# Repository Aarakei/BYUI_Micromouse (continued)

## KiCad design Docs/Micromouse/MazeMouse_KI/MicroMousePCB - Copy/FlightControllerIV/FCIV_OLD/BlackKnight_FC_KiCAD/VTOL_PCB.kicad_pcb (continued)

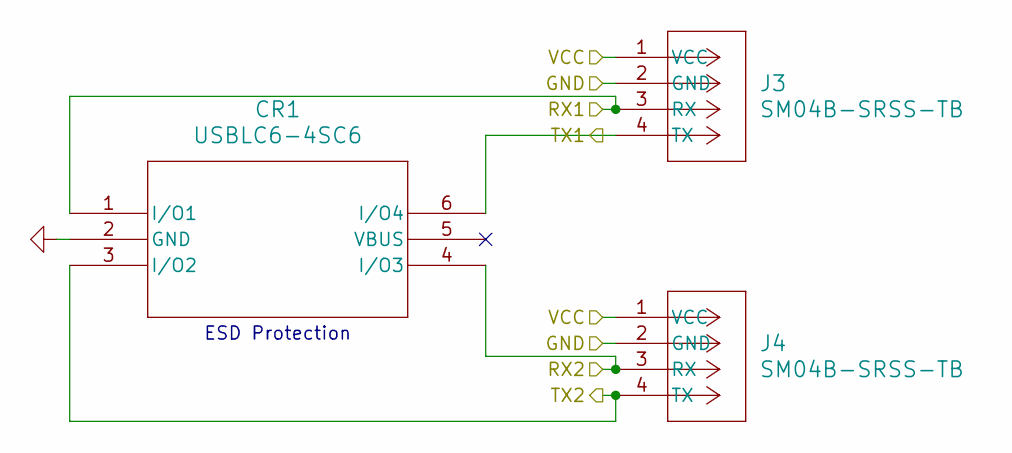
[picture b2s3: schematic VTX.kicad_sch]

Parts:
CR1: USBLC6-4SC6; SOT23-6L_STM; Manufacturer_Part_Number USBLC6-4SC6; JLCPCB Part # C111212
J3, J4: SM04B-SRSS-TB; JST_SH_SM04B-SRSS-TB_1x04-1MP_P1.00mm_Horizontal; Manufacturer_Part_Number XY-SM04B-SRSS-TB; JLCPCB Part # C160404

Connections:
9V_3A: J3.1 (VCC), J4.1 (VCC); also elsewhere on the board
/STM32F722VET6/UART4_RX: CR1.6 (I/O4), J3.4 (TX); also elsewhere on the board
/STM32F722VET6/UART4_TX: CR1.1 (I/O1), J3.3 (RX); also elsewhere on the board
/STM32F722VET6/USART2_RX: CR1.4 (I/O3), J4.3 (RX); also elsewhere on the board
/STM32F722VET6/USART2_TX: CR1.3 (I/O2), J4.4 (TX); also elsewhere on the board
GND: CR1.2 (GND), J3.2 (GND), J4.2 (GND); also elsewhere on the board

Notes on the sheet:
ESD Protection

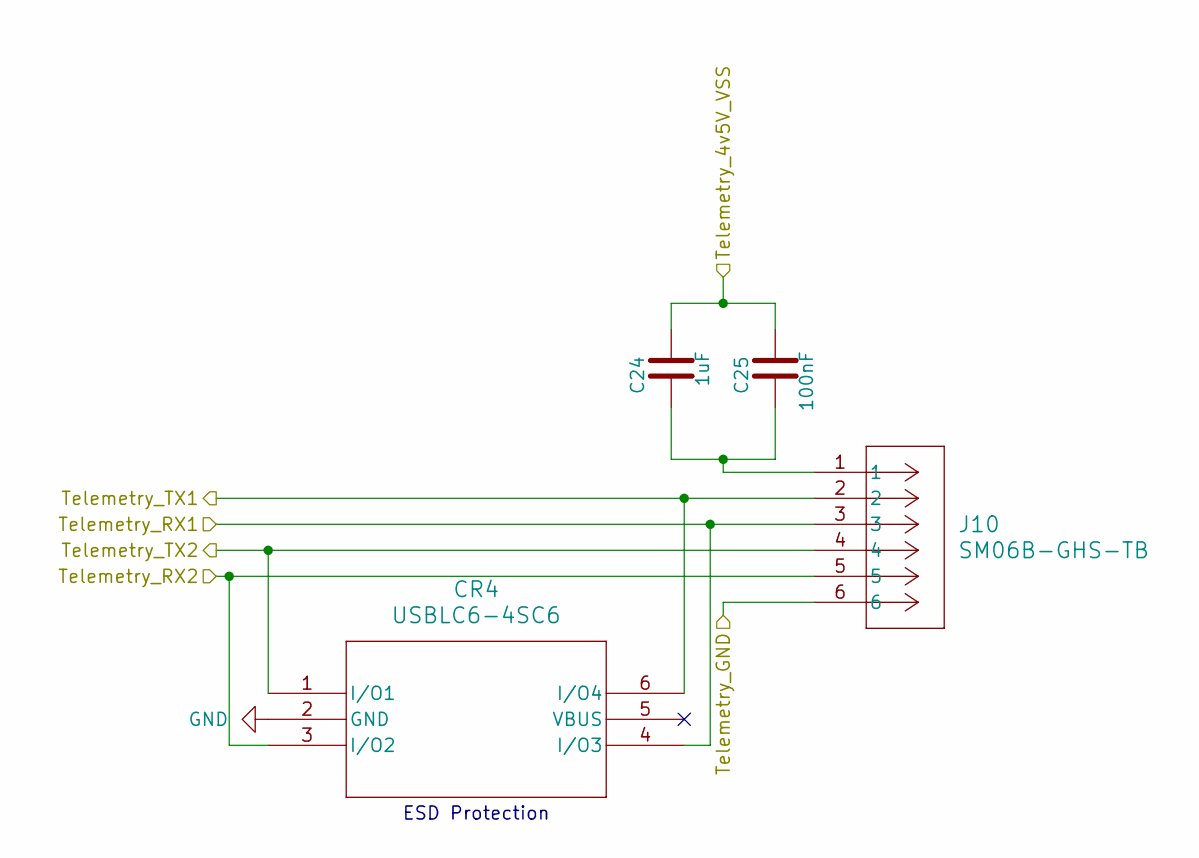
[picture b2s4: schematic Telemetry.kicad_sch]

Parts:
C24: 1uF; C_0603_1608Metric; Manufacturer_Part_Number C0603C104K5RACTU; JLCPCB Part # C15849
C25: 100nF; C_0603_1608Metric; JLCPCB Part # C1591
CR4: USBLC6-4SC6; SOT23-6L_STM; Manufacturer_Part_Number USBLC6-4SC6; JLCPCB Part # C111212
J10: SM06B-GHS-TB; CONN_SM06B-GHS-TB_JST; Manufacturer_Part_Number SM06B-GHS-TB; JLCPCB Part # C133065

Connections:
5.2V_To_Power_Plane: C24.1, C25.1; also elsewhere on the board
/STM32F722VET6/UART7_RX: CR4.1 (I/O1), J10.4; also elsewhere on the board
/STM32F722VET6/UART7_TX: CR4.3 (I/O2), J10.5; also elsewhere on the board
/STM32F722VET6/USART6_RX: CR4.6 (I/O4), J10.2; also elsewhere on the board
/STM32F722VET6/USART6_TX: CR4.4 (I/O3), J10.3; also elsewhere on the board
GND: CR4.2 (GND), J10.6; also elsewhere on the board
unnamed: C24.2, C25.2, J10.1

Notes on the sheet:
ESD Protection

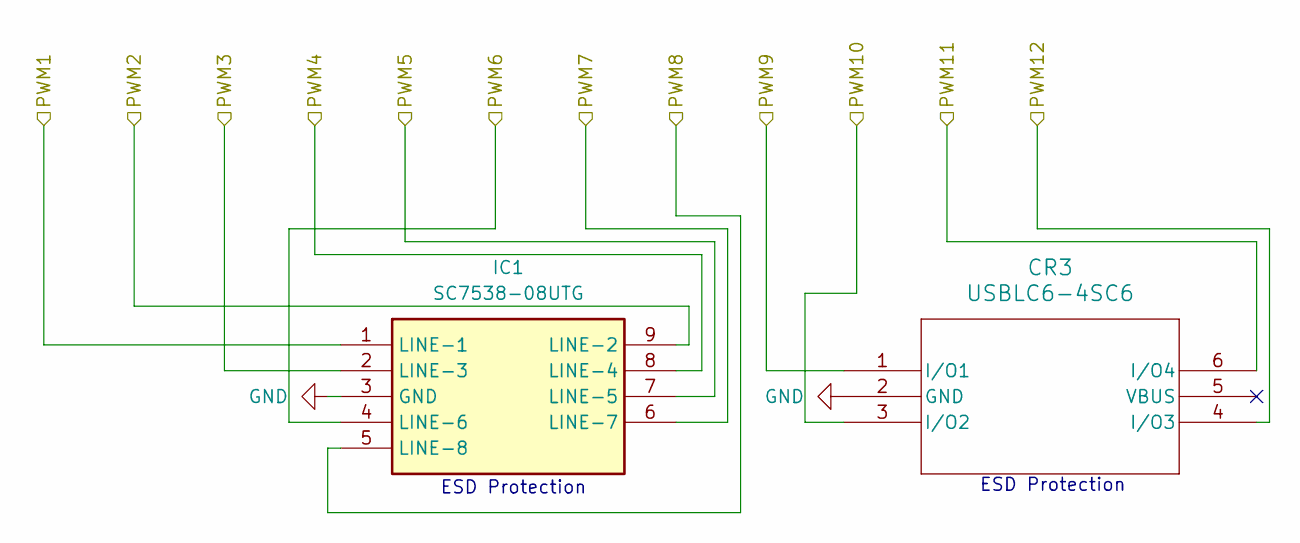
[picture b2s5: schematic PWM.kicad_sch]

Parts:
CR3: USBLC6-4SC6; SOT23-6L_STM; Manufacturer_Part_Number USBLC6-4SC6; JLCPCB Part # C111212
IC1: SC7538-08UTG; SC753808UTG; Mouser Part Number 576-SC7538-08UTG

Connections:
/PWM/PWM1: IC1.1 (LINE-1); also elsewhere on the board
/PWM/PWM2: IC1.9 (LINE-2); also elsewhere on the board
/PWM/PWM3: IC1.2 (LINE-3); also elsewhere on the board
/PWM/PWM4: IC1.8 (LINE-4); also elsewhere on the board
/PWM/PWM5: IC1.7 (LINE-5); also elsewhere on the board
/PWM/PWM6: IC1.4 (LINE-6); also elsewhere on the board
/PWM/PWM7: IC1.6 (LINE-7); also elsewhere on the board
/PWM/PWM8: IC1.5 (LINE-8); also elsewhere on the board
/PWM/PWM9: CR3.1 (I/O1); also elsewhere on the board
/PWM/PWM10: CR3.3 (I/O2); also elsewhere on the board
/PWM/PWM11: CR3.6 (I/O4); also elsewhere on the board
/PWM/PWM12: CR3.4 (I/O3); also elsewhere on the board
GND: CR3.2 (GND), IC1.3 (GND); also elsewhere on the board

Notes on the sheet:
ESD Protection

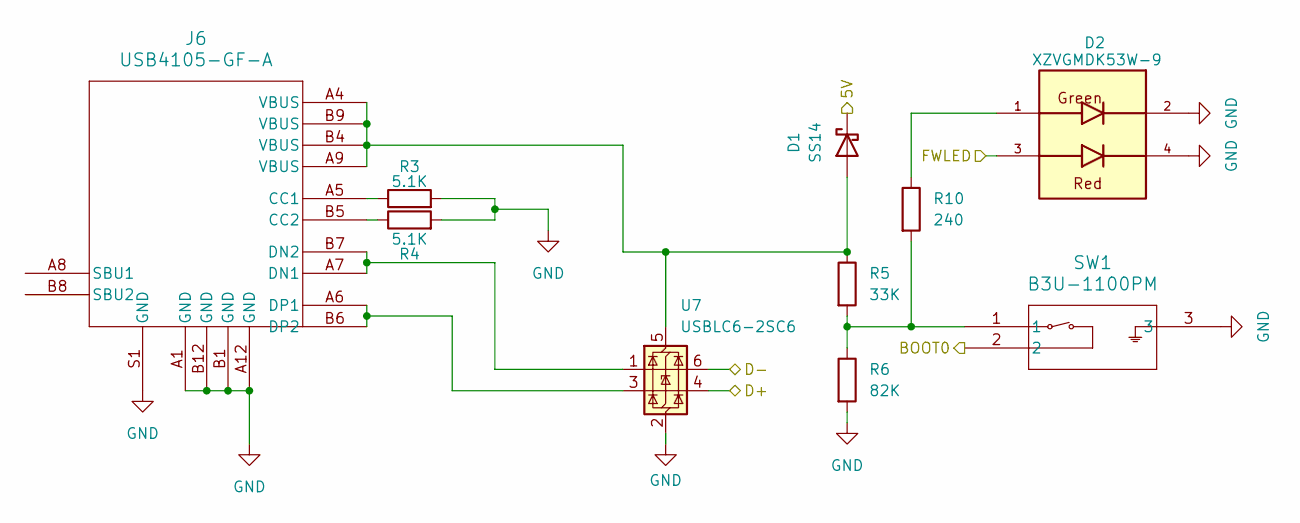
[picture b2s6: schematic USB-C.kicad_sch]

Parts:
D1: SS14; D_SMA; Manufacturer_Part_Number SS14; JLCPCB Part # C83852
D2: XZVGMDK53W-9; LED_XZVGMDK53W-9; Manufacturer_Part_Number XZVGMDK53W-9; JLCPCB Part # C6506245
J6: USB4105-GF-A; USB_C_Receptacle_GCT_USB4105-xx-A_16P_TopMnt_Horizontal; Manufacturer_Part_Number USB4105-GF-A; JLCPCB Part # C3020560
R3, R4: 5.1K; R_0603_1608Metric; Manufacturer_Part_Number RC0603FR-075K1L; JLCPCB Part # C105580
R5: 33K; R_0603_1608Metric; Manufacturer_Part_Number RC0603FR-0733KL; JLCPCB Part # C126359
R6: 82K; R_0603_1608Metric; Manufacturer_Part_Number RC0603JR-0782KL; JLCPCB Part # C137678
R10: 240; R_0603_1608Metric; Manufacturer_Part_Number RC0603FR-07240RL; JLCPCB Part # C114613
SW1: B3U-1100PM; Boot_Button_Footprint; Manufacturer_Part_Number B3U-1100P; JLCPCB Part # C6467298
U7: USBLC6-2SC6; SOT23-6L_STM; Manufacturer_Part_Number USBLC6-2SC6; JLCPCB Part # C7519

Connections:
5.2V_To_Power_Plane: D1.1 (K); also elsewhere on the board
/STM32F722VET6/FWLED: D2.3; also elsewhere on the board
/STM32F722VET6/USB_OTG_FS_DM: U7.6 (I/O1); also elsewhere on the board
/STM32F722VET6/USB_OTG_FS_DP: U7.4 (I/O2); also elsewhere on the board
GND: D2.2, D2.4, J6.A1 (GND), J6.A12 (GND), J6.B1 (GND), J6.B12 (GND), J6.S1 (GND), R3.2, R4.2, R6.2, SW1.3, U7.2 (GND); also elsewhere on the board
unnamed: D1.2 (A), J6.A4 (VBUS), J6.A9 (VBUS), J6.B4 (VBUS), J6.B9 (VBUS), R5.1, U7.5 (VBUS)
unnamed: D2.1, R10.1
unnamed: J6.A5 (CC1), R3.1
unnamed: J6.B5 (CC2), R4.1
unnamed: J6.A7 (DN1), J6.B7 (DN2), U7.1 (I/O1)
unnamed: J6.A6 (DP1), J6.B6 (DP2), U7.3 (I/O2)
unnamed: R5.2, R6.1, R10.2, SW1.1
WB_BOOT0: SW1.2; also elsewhere on the board

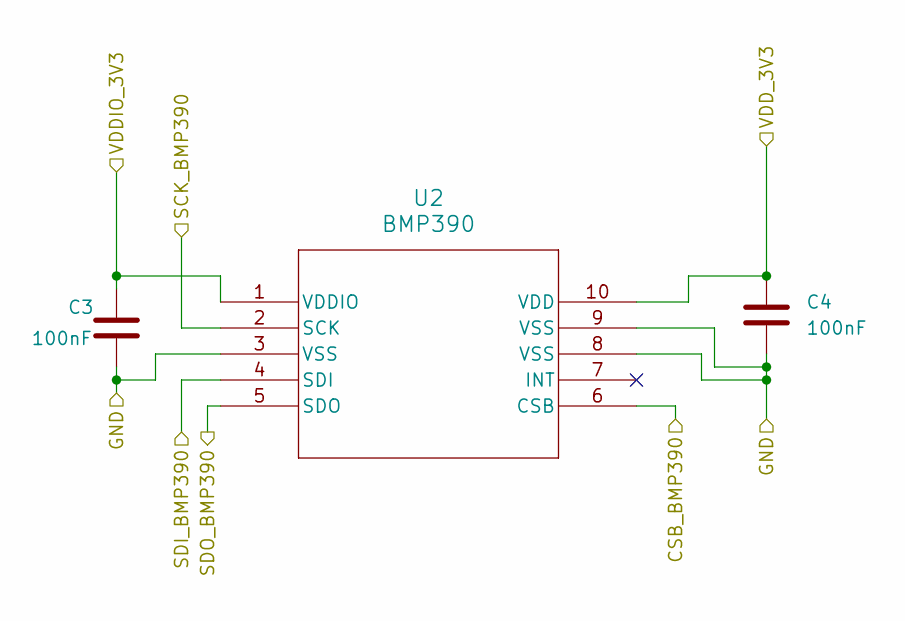
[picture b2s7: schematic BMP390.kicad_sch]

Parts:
C3, C4: 100nF; C_0603_1608Metric; Manufacturer_Part_Number CL10B104KA8NNNC; JLCPCB Part # C1591
U2: BMP390; 10LGA_2X2X0p75_BOS; Manufacturer_Part_Number BMP390; JLCPCB Part # C5124834

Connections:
3.3V_To_Power_Plane: C3.2, C4.1, U2.1 (VDDIO), U2.10 (VDD); also elsewhere on the board
/BMP390/CSB_BMP390: U2.6 (CSB); also elsewhere on the board
/BMP390/SCK_BMP390: U2.2 (SCK); also elsewhere on the board
/BMP390/SDI_BMP390: U2.4 (SDI); also elsewhere on the board
/BMP390/SDO_BMP390: U2.5 (SDO); also elsewhere on the board
GND: C3.1, C4.2, U2.3 (VSS), U2.8 (VSS), U2.9 (VSS); also elsewhere on the board

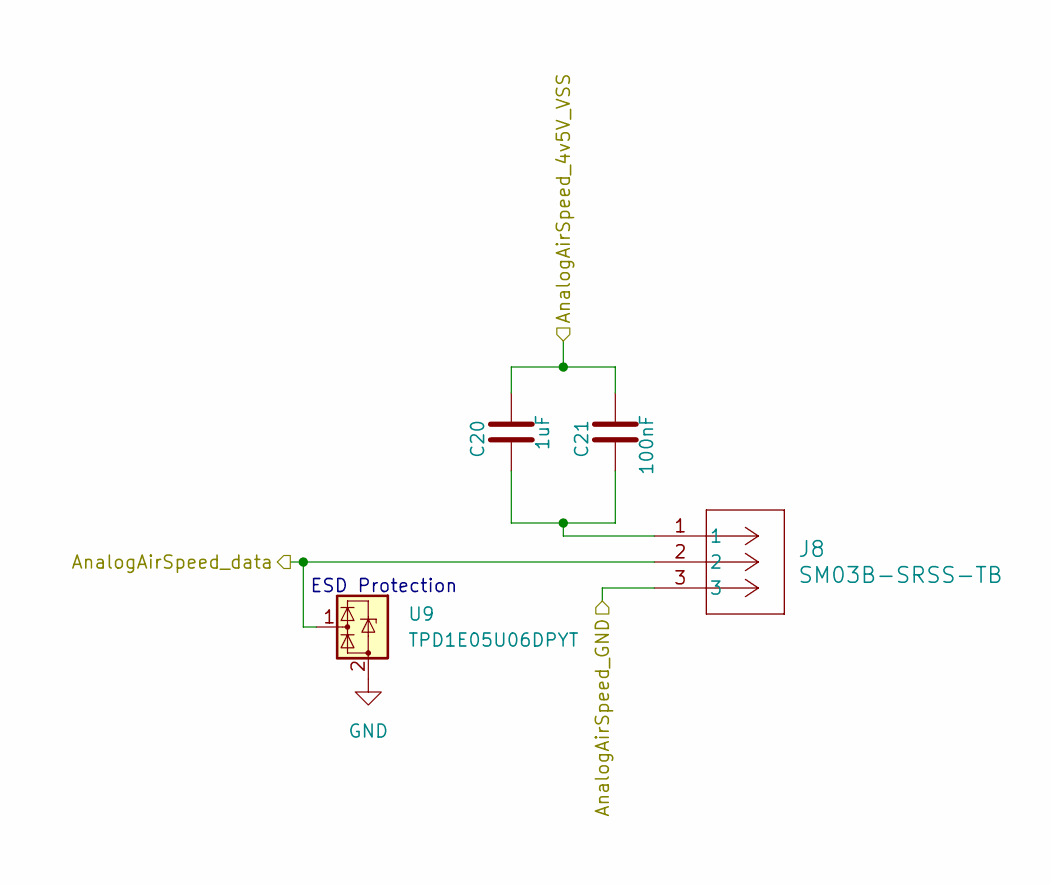
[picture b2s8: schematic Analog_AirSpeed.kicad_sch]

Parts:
C20: 1uF; C_0603_1608Metric; Manufacturer_Part_Number C0603C104K5RACTU; JLCPCB Part # C15849
C21: 100nF; C_0603_1608Metric; JLCPCB Part # C1591
J8: SM03B-SRSS-TB; 3pin_SM03B-SRSS-TB_JST; Manufacturer_Part_Number SM03B-SRSS-TB; JLCPCB Part # C160403
U9: TPD1E05U06DPYT; Texas_DPY0002A_0.6x1mm_P0.65mm; Manufacturer_Part_Number TPD1E05U06DPYT; JLCPCB Part # C1847651

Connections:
5.2V_To_Power_Plane: C20.1, C21.1; also elsewhere on the board
/Analog_AirSpeed/AnalogAirSpeed_data: J8.2, U9.1 (I/O); also elsewhere on the board
GND: J8.3, U9.2 (GND); also elsewhere on the board
unnamed: C20.2, C21.2, J8.1

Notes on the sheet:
ESD Protection

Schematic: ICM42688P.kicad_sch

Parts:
C5: 10uF; C_0603_1608Metric; Manufacturer_Part_Number KAM15CT70E106KT; JLCPCB Part # C19702
C6: 100nF; C_0603_1608Metric; Manufacturer_Part_Number CL10B104KA8NNNC; JLCPCB Part # C1591
C7: 2.2uF; C_0603_1608Metric; Manufacturer_Part_Number CL10A225KO8NNNC; JLCPCB Part # C23630
U3: ICM-42688-P; LGA14_2P5X3X0P91_TDK; Manufacturer_Part_Number ICM-42688-P; JLCPCB Part # C1850418

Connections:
3.3V_To_Power_Plane: C5.1, C6.2, C7.2, U3.5 (VDDIO), U3.8 (VDD); also elsewhere on the board
/ICM42688P_IMU/ICM_CLKIN: U3.9 (INT2/FSYNC/CLKIN); also elsewhere on the board
/ICM42688P_IMU/ICM_CS: U3.12 (AP_CS); also elsewhere on the board
/ICM42688P_IMU/ICM_INT1: U3.4 (INT1/INT)
/ICM42688P_IMU/ICM_SCLK: U3.13 (AP_SCL/AP_SCLK); also elsewhere on the board
/ICM42688P_IMU/ICM_SDI: U3.14 (AP_SDA/AP_SDIO/AP_SDI); also elsewhere on the board
/ICM42688P_IMU/ICM_SDO: U3.1 (AP_SDO/AP_AD0); also elsewhere on the board
GND: C5.2, C6.1, C7.1, U3.6 (GND), U3.7 (RESV); also elsewhere on the board

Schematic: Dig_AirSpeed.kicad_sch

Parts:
C18: 4.7uF; C_0603_1608Metric; Manufacturer_Part_Number CL10A475KP8NNNC; JLCPCB Part # C19666
C19: 100nF; C_0603_1608Metric; JLCPCB Part # C1591
J7: SM04B-GHS-TB; JST_GH_SM04B-GHS-TB_1x04-1MP_P1.25mm_Horizontal; Manufacturer_Part_Number SM04B-GHS-TB; JLCPCB Part # C189895
R7, R8: 4.7k; R_0603_1608Metric; Manufacturer_Part_Number RC0603JR-074K7L; JLCPCB Part # C99782
U8: USBLC6-2SC6; SOT23-6L_STM; Manufacturer_Part_Number USBLC6-2SC6; JLCPCB Part # C7519

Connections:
3.3V_To_Power_Plane: R7.2, R8.2; also elsewhere on the board
5.2V_To_Power_Plane: C18.1, C19.1; also elsewhere on the board
/Dig_AirSpeed/Dig_AirSpeed_Rx: R7.1, U8.1 (I/O1); also elsewhere on the board
/Dig_AirSpeed/Dig_AirSpeed_Tx: R8.1, U8.3 (I/O2); also elsewhere on the board
GND: J7.2 (GND), U8.2 (GND); also elsewhere on the board
unnamed: J7.3 (RX), U8.6 (I/O1)
unnamed: J7.4 (TX), U8.4 (I/O2)
unnamed: C18.2, C19.2, J7.1 (VCC)

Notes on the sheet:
ESD Protection

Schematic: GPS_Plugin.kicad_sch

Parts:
C16: 4.7uF; C_0603_1608Metric; Manufacturer_Part_Number CL10A475KP8NNNC; JLCPCB Part # C19666
C17: 100nF; C_0603_1608Metric; JLCPCB Part # C1591
CR2: USBLC6-4SC6; SOT23-6L_STM; Manufacturer_Part_Number USBLC6-4SC6; JLCPCB Part # C111212
J5: SM06B-SRSS-TB(LF)(SN); JST_SH_SM06B-SRSS-TB_1x06-1MP_P1.00mm_Horizontal; Manufacturer_Part_Number SM06B-SRSS-TB(LF)(SN); JLCPCB Part # C160405
R1, R2: 4.7k; R_0603_1608Metric; Manufacturer_Part_Number RC0603JR-074K7L; JLCPCB Part # C99782

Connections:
3.3V_To_Power_Plane: R1.2, R2.2; also elsewhere on the board
5.2V_To_Power_Plane: C16.1, C17.1; also elsewhere on the board
GND: CR2.2 (GND), J5.6; also elsewhere on the board
unnamed: C16.2, C17.2, J5.1
WB_GPS_RX: CR2.3 (I/O2), J5.3; also elsewhere on the board
WB_GPS_TX: CR2.1 (I/O1), J5.2; also elsewhere on the board
WB_I2C_SCL: CR2.6 (I/O4), J5.4, R1.1; also elsewhere on the board
WB_I2C_SDA: CR2.4 (I/O3), J5.5, R2.1; also elsewhere on the board

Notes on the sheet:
ESD Protection

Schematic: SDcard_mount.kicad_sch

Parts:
C10: 4.7uF; C_0603_1608Metric; Manufacturer_Part_Number CL10A475KP8NNNC; JLCPCB Part # C19666
C11: 100nF; C_0603_1608Metric; JLCPCB Part # C1591
J11: Micro_SD_Card_Det1; microSD_HC_Hirose_DM3D-SF; JLCPCB Part # C719027
U5: EMIF06-MSD02N16; QFN-16L_L3.5-W1.2-P0.40_EMIF06-MSD02N16; Manufacturer_Part_Number EMIF06-MSD02N16; JLCPCB Part # C5267594

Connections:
3.3V_To_Power_Plane: C10.1, C11.1, J11.4 (VDD), U5.16 (VCC), U5.17 (RDAT_VCC); also elsewhere on the board
/SDcard_mount/CD/DAT3: U5.4 (DAT3_IN); also elsewhere on the board
/SDcard_mount/CLK: U5.6 (CLK_IN); also elsewhere on the board
/SDcard_mount/CMD: U5.5 (CMD_IN); also elsewhere on the board
/SDcard_mount/DAT0: U5.7 (DAT0_IN); also elsewhere on the board
/SDcard_mount/DAT1: U5.8 (DAT1_IN); also elsewhere on the board
/SDcard_mount/DAT2: U5.3 (DAT2_IN); also elsewhere on the board
GND: C10.2, C11.2, J11.6 (VSS), J11.10 (SHIELD), U5.9 (GND), U5.18 (GND), U5.19 (GND); also elsewhere on the board
unnamed: J11.5 (CLK), U5.12 (CLK_EX)
unnamed: J11.3 (CMD), U5.13 (CMD_EX)
unnamed: J11.7 (DAT0), U5.11 (DAT0_EX)
unnamed: J11.8 (DAT1), U5.10 (DAT1_EX)
unnamed: J11.1 (DAT2), U5.15 (DAT2_EX)
unnamed: J11.2 (DAT3/CD), U5.14 (DAT3_EX)
unnamed: J11.9 (DET), U5.1 (WP/CD)

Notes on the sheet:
decoupling cap, and filter cap
ESD Protection

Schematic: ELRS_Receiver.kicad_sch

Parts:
C22: 1uF; C_0603_1608Metric; Manufacturer_Part_Number C0603C104K5RACTU; JLCPCB Part # C15849
C23: 100nF; C_0603_1608Metric; JLCPCB Part # C1591
J9: SM04B-SRSS-TB; JST_SH_SM04B-SRSS-TB_1x04-1MP_P1.00mm_Horizontal; Manufacturer_Part_Number XY-SM04B-SRSS-TB; JLCPCB Part # C160404
U10: USBLC6-2SC6; SOT23-6L_STM; Manufacturer_Part_Number USBLC6-2SC6; JLCPCB Part # C7519

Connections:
5.2V_To_Power_Plane: C22.1, C23.1; also elsewhere on the board
GND: J9.2 (GND), U10.2 (GND); also elsewhere on the board
unnamed: J9.3 (RX), U10.6 (I/O1)
unnamed: J9.4 (TX), U10.4 (I/O2)
unnamed: C22.2, C23.2, J9.1 (VCC)
WB_ELRS_RX: U10.1 (I/O1); also elsewhere on the board
WB_ELRS_TX: U10.3 (I/O2); also elsewhere on the board

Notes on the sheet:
ESD Protection

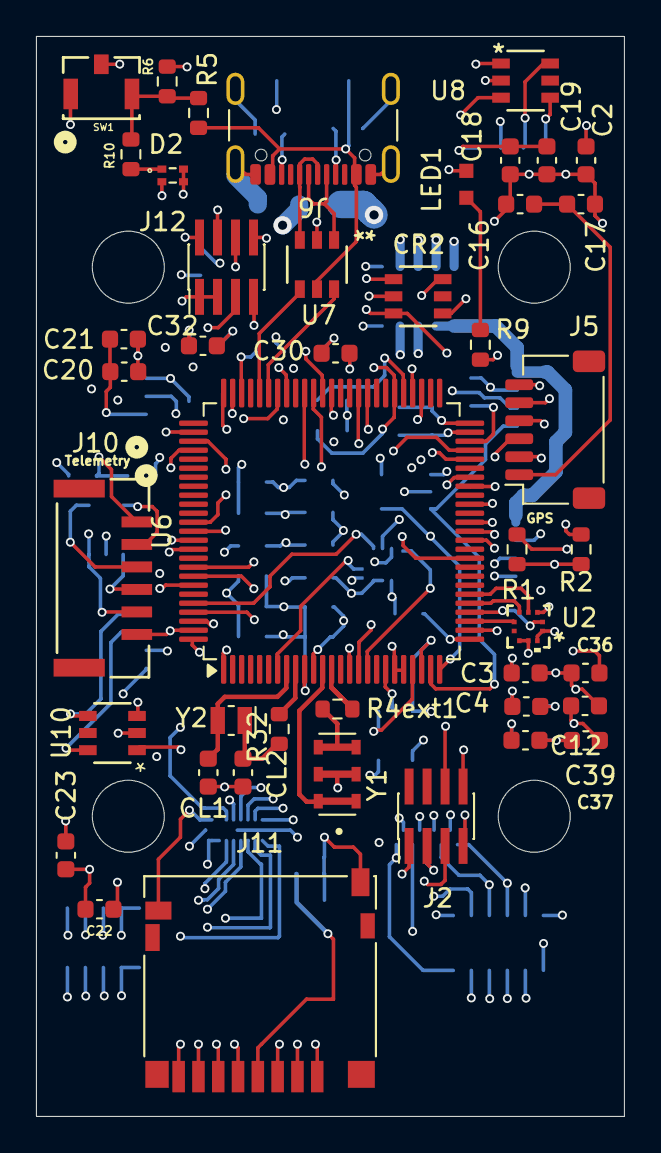
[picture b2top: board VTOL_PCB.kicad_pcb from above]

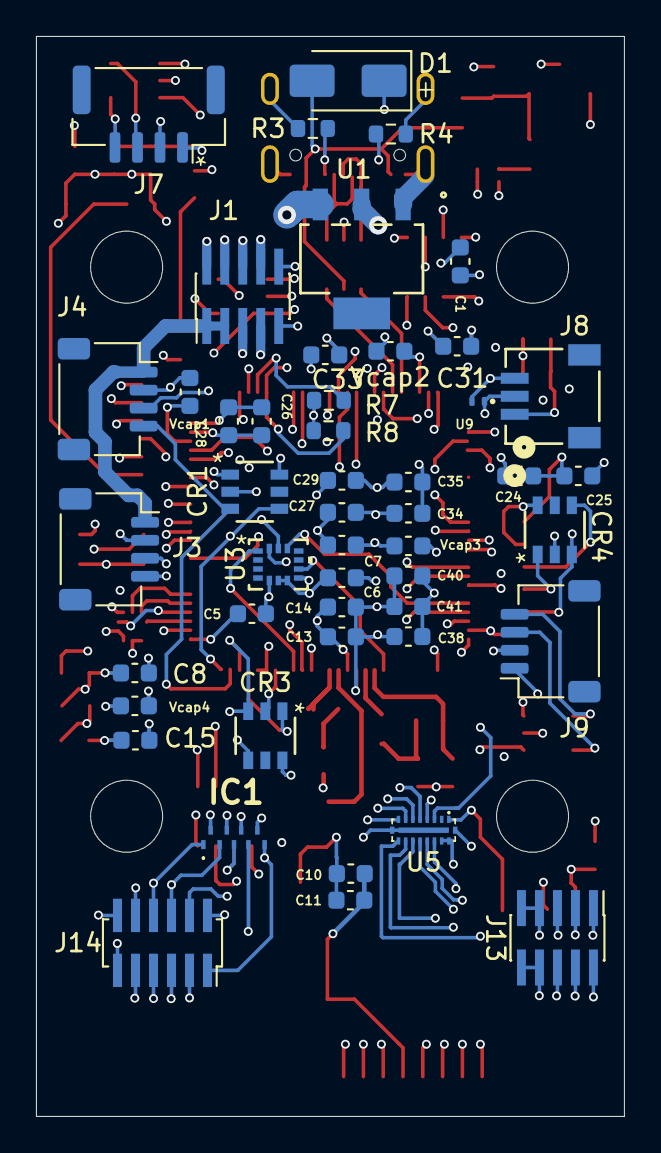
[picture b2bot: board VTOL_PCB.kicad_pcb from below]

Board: 6 copper layers, 32.7 x 60.0 mm, 92 parts (48 on the bottom side), 85 nets.

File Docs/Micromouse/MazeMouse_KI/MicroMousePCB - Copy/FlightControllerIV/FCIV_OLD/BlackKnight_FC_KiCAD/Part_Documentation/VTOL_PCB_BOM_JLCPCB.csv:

"Value","Reference","Footprint","Qty","JLCPCB Part #","Recommended American Manufacturer Part","Notes"
"22uF","C1","Capacitor_SMD:C_0603_1608Metric","1","C86295","samsung CL10A226MP8NUNE",""
"10uF","C2,C5","Capacitor_SMD:C_0603_1608Metric","2","C19702","samsung CL10A106KP8NNNC",""
"100nF","C3,C4,C6,C8,C11,C12,C13,C14,C15,C17,C19,C21,C23,C25,C26,C27,C28,C29,C30,C31,C32,C33,C34,C35,C36,C37,C38,C39,C40,C41","Capacitor_SMD:C_0603_1608Metric","30","C1591","samsung CL10B104KB8NNNC",""
"2.2uF","C7,Vcap1,Vcap2","Capacitor_SMD:C_0603_1608Metric","3","C23630","samsung CL10A225KO8NNNC",""
"4.7uF","C10,C16,C18,Vcap3","Capacitor_SMD:C_0603_1608Metric","4","C19666","samsung CL10A475KO8NNNC",""
"1uF","C20,C22,C24,Vcap4","Capacitor_SMD:C_0603_1608Metric","4","C15849","samsung CL10A105KB8NNNC",""
"8pF","CL1,CL2","Capacitor_SMD:C_0603_1608Metric","2","C346204","samsung CL10C080DB81PNC",""
"USBLC6-4SC6","CR1,CR2,CR3,CR4","USBC6-4SC6 footprint:SOT23-6L_STM","4","C111212","ST USBLC6-4SC6",""
"SS14","D1","Diode_SMD:D_SMA","1","C83852","onsemi SS14",""
"XZVGMDK53W-9","D2","XZVGMDK53W_9:LED_XZVGMDK53W-9","1","C6506245","SunLED - XZVGMDK53W-9","JLCPCB part number for american IC: C6759211"
"SC7538-08UTG","IC1","SC7538-08_footprint:SC753808UTG","1","C3706365","Littelfuse SC7538-08UTG","PWM ESD protection module"
"BC050-10A-K0-0200-0160-0480-LB","J1,J13","Connector_PinHeader_1.00mm:PinHeader_2x05_P1.00mm_Vertical_SMD","2","C5952679","Global Connector Technology BC050-10A-K0-0200-0160-0480-LB",""
"BC050-08A-K0-0200-0160-0480-LB","J2,J12","Connector_PinHeader_1.00mm:PinHeader_2x04_P1.00mm_Vertical_SMD","2","C5557054 ","Global Connector Technology Global Connector Technology BC050-08A-K0-0200-0160-0480-LB",""
"SM04B-SRSS-TB","J3,J4,J9","Connector_JST:JST_SH_SM04B-SRSS-TB_1x04-1MP_P1.00mm_Horizontal","3","C160404","JST SM04B-SRSS-TB",""
"SM06B-SRSS-TB(LF)(SN)","J5","Connector_JST:JST_SH_SM06B-SRSS-TB_1x06-1MP_P1.00mm_Horizontal","1","C160405","JST SM06B-SRSS-TB",""
"USB4105-GF-A","J6","Connector_USB:USB_C_Receptacle_GCT_USB4105-xx-A_16P_TopMnt_Horizontal","1","C3020560","Global Connector Technology USB4105-GF-A","USB-C connection"
"SM04B-GHS-TB","J7","Connector_JST:JST_GH_SM04B-GHS-TB_1x04-1MP_P1.25mm_Horizontal","1","C189895","JST SM04B-GHS-TB",""
"SM03B-SRSS-TB","J8","3pin_SM03B-SRSS-TB_JST:3pin_SM03B-SRSS-TB_JST","1","C160403 ","JST SM03B-SRSS-TB",""
"SM06B-GHS-TB","J10","6pin_JST_SM06B-GHS-TB:CONN_SM06B-GHS-TB_JST","1","C133065","JST SM06B-GHS-TB",""
"Micro_SD_Card_Det1","J11","Connector_Card:microSD_HC_Hirose_DM3D-SF","1","C719027","Hirose DM3D-SF",""
"BC085-12-A-0390-L-C","J14","Connector_PinSocket_1.00mm:PinSocket_2x06_P1.00mm_Vertical_SMD","1","C5952752","Global Connector Technologies BC085-12-A-0390-L-C",""
"LTST-C190GKT","LED1","LTST_C190GKT:LTST-C190CKT","1","C125093","Lite-On Inc. LTST-C190GKT",""
"4.7k","R1,R2,R7,R8","Resistor_SMD:R_0603_1608Metric","4","C99782","YAGEO RC0603FR-074K7L",""
"5.1K","R3,R4","Resistor_SMD:R_0603_1608Metric","2","C105580","YAGEO RC0603FR-075K1L",""
"100","R4ext1,R32","Resistor_SMD:R_0603_1608Metric","2","C105588","YAGEO RC0603FR-07100RL",""
"33K","R5","Resistor_SMD:R_0603_1608Metric","1","C126359","YAGEO RC0603FR-0733KL",""
"82K","R6","Resistor_SMD:R_0603_1608Metric","1","C137678","YAGEO RC0603FR-0782KL",""
"240","R9,R10","Resistor_SMD:R_0603_1608Metric","2","C114613","YAGEO RC0603FR-07240RL",""
"B3U-1100PM","SW1","Boot_Button_Footprint:Boot_Button_Footprint","1","C6467298","OMRON B3U-1100PM","pin 1 in Kicad is pin 2 on the selected part datasheet and visa verse"
"AZ1117CH-3.3TRG1","U1","AZ1117CH_3_3TRG1:SOT-223_DIO","1","C92102","DIODES AZ1117CH-3.3TRG1","Linear regulator max "
"BMP390","U2","footprints:10LGA_2X2X0p75_BOS","1","C5124834","Bosch BMP390","Pressure Sensor"
"ICM-42688-P","U3","ICM_footprints:LGA14_2P5X3X0P91_TDK","1","C1850418","TDK InvenSense ICM-42688-P",""
"EMIF06-MSD02N16","U5","footprints:QFN-16L_L3.5-W1.2-P0.40_EMIF06-MSD02N16","1","C5267594","ST EMIF06-MSD02N16",""
"STM32F722VET6","U6","Package_QFP:LQFP-100_14x14mm_P0.5mm","1","C132372","",""
"USBLC6-2SC6","U7,U8,U10","USBC6-4SC6 footprint:SOT23-6L_STM","3","C7519","ST USBLC6-2SC6",""
"TPD1E05U06DPYT","U9","Package_SON:Texas_DPY0002A_0.6x1mm_P0.65mm","1","C1847651","TI TPD1E05U06DPYT",""
"CSTCR4M00G55-R0","Y1","CSTCR4:OSC_CSTCR4M00G55-R0","1","C91588","muRata CSTCR4M00G55-R0",""
"CM8V-T1A-32.768KHZ-7PF-20PPM-TA-QC","Y2","Crystal:Crystal_SMD_MicroCrystal_CC8V-T1A-2Pin_2.0x1.2mm","1","C5136974","Micro Crystal CM8V-T1A-32.768KHZ-7PF-20PPM-TA-QC",""

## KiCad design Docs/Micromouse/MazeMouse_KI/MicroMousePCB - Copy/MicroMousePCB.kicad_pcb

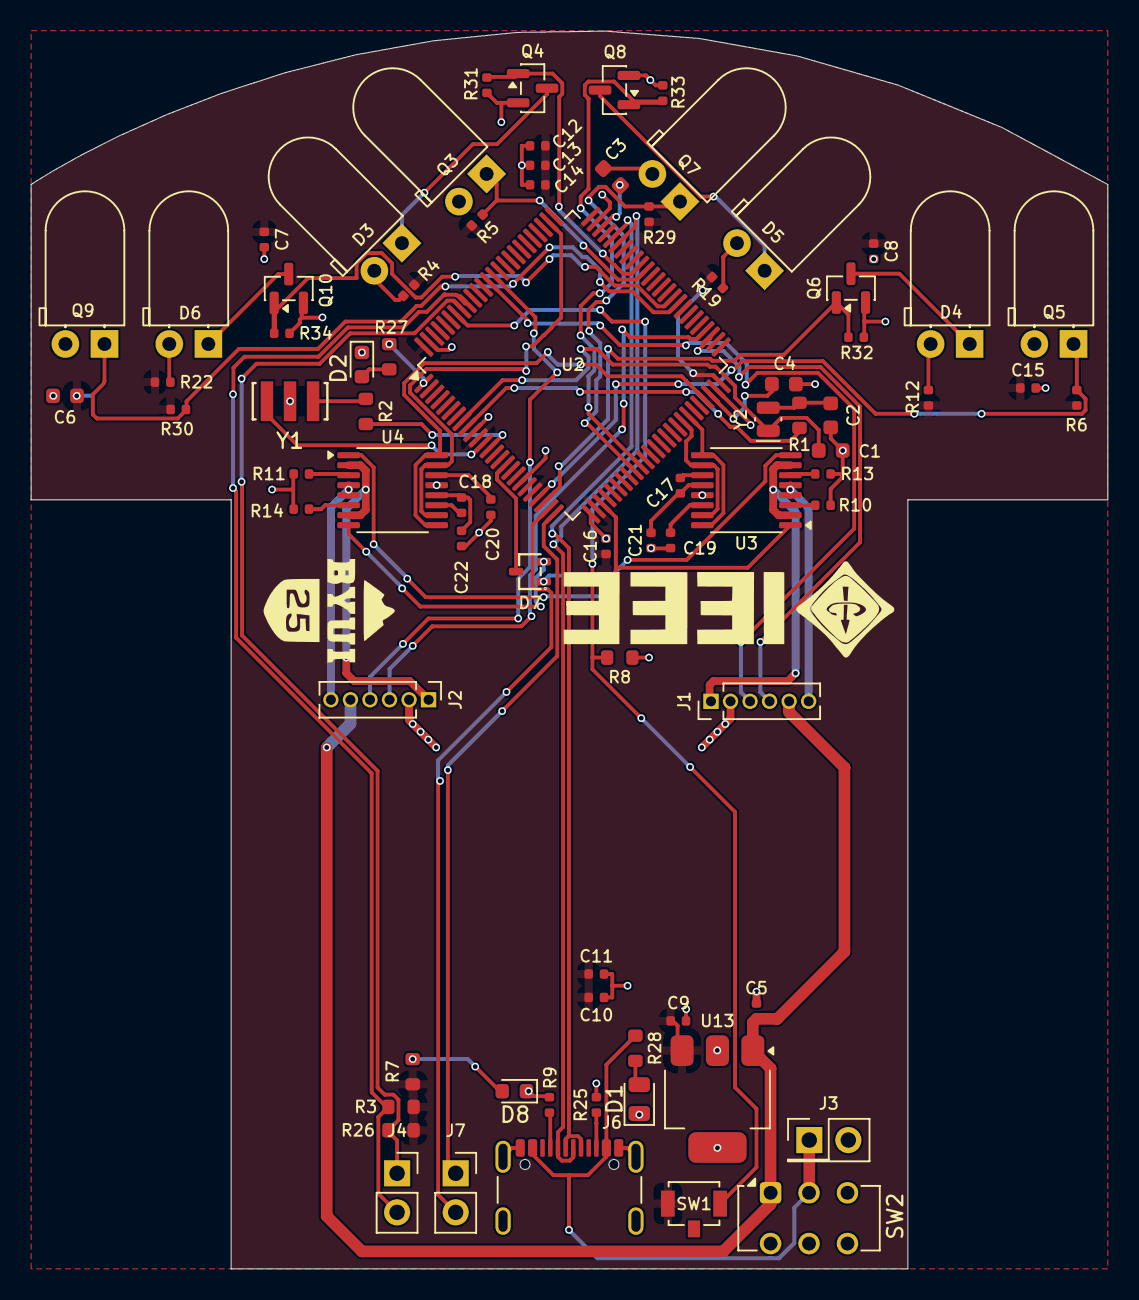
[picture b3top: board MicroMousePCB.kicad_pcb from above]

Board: 2 copper layers, 70.0 x 80.5 mm, 78 parts (0 on the bottom side), 67 nets.

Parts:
C1, C2: 10pF; C_0603
C3, C4: 2.2uF; C_0603
C5, C21, C22: 10uF; C_0402
C6: 22uF; C_0603
C7, C8, C9, C10, C11, C12, C13, C14, C15, C16: 100nF; C_0402
C17, C18: 10nF; C_0402
C19, C20: 2.2uF; C_0402
D1: Green; LED_0805_2012Metric
D2: Red; LED_0603_1608Metric
D3, D4, D5, D6: IR204A; LED_D5.0mm_Horizontal_O1.27mm_Z3.0mm_IRBlack
D7: BAT54AW; SOT-323-3_L2.0-W1.3-P1.30-LS2.3-BR
D8: LTST-C190GKT; LED_0603_1608Metric
J1, J2: Conn_01x06_Pin; PinHeader_1x06_P1.27mm_Vertical
J3: Battery; PinHeader_2x01_P2.54mm_Vertical
J4, J7: Conn_01x02_Socket; PinSocket_1x02_P2.54mm_Vertical
J6: USB_C_Receptacle_USB2.0_16P; USB_C_Receptacle_GCT_USB4105-xx-A_16P_TopMnt_Horizontal
Q3, Q5, Q7, Q9: SFH300; LED_D5.0mm_Horizontal_O1.27mm_Z3.0mm_Clear
Q4, Q6, Q8, Q10: AO3400A; SOT-23
R1, R2: 100Ω; R_0603
R3, R8, R26: 1.8kΩ; R_0603
R4, R12, R19, R22: 100Ω; R_0402
R5, R6, R29, R30, R31, R32, R33, R34: 1kΩ; R_0402
R7, R27, R28: 240Ω; R_0603
R9, R25: 5.1kΩ; R_0402
R10, R11, R13, R14: 0Ω; R_0402
SW1: SW_Push; SW_SPST_B3U-1100P
SW2: SW_DPDT_x2; SW_CK_JS202011CQN_DPDT_Straight
U2: STM32H743VITx; LQFP-100_14x14mm_P0.5mm
U3, U4: DRV8833PWP; TSSOP-16_4.4x5mm_P0.65mm
U13: AZ1117CH2-3.3; SOT-223-3_TabPin2
Y1: 8MHz Resonator *4MHz*; CSTCR_G_MUR
Y2: 32.768 kHz Resonator; Crystal_SMD_MicroCrystal_CC8V-T1A-2Pin_2.0x1.2mm

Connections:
1C1: J2.3, U2.54 (PB15)
1C2: J2.4, U2.87 (PD6)
1in1: U2.47 (PB11), U4.9 (BIN1), U4.16 (AIN1)
1in2: U2.77 (PA15), U4.10 (BIN2), U4.15 (AIN2)
2C1: J1.3, U2.88 (PD7)
2C2: J1.4, U2.53 (PB14)
2in1: U2.44 (PE14), U3.9 (BIN1), U3.16 (AIN1)
2in2: U2.43 (PE13), U3.10 (BIN2), U3.15 (AIN2)
3.3V: C6.1, C7.1, C8.1, C9.1, C10.1, C11.1, C12.1, C13.1, C14.1, C15.1, C16.1, R3.2, R4.1, R5.1, R6.1, R7.1, R12.1, R19.1, R22.1, R26.2, R29.1, R30.1, SW1.1, U2.11 (VDD), U2.21 (VDDA), U2.27 (VDD), U2.50 (VDD), U2.75 (VDD), U2.100 (VDD), U13.3 (OUT)
/Motor1/Aout1: J2.1, U4.2 (AOUT1), U4.7 (BOUT1)
/Motor1/Aout2: J2.6, U4.4 (AOUT2), U4.5 (BOUT2)
/Motor1/VM: C18.1, C22.1, U4.12 (VM)
/Motor/Aout1: J1.1, U3.2 (AOUT1), U3.7 (BOUT1)
/Motor/Aout2: J1.6, U3.4 (AOUT2), U3.5 (BOUT2)
/Motor/VM: C17.1, C21.1, U3.12 (VM)
/STM32H743VIH6/FWLED: R27.2, U2.1 (PE2)
/STM32H743VIH6/I2C1_SCL: J4.2, R3.1, U2.92 (PB6)
/STM32H743VIH6/I2C1_SDA: J4.1, R26.1, U2.93 (PB7)
/STM32H743VIH6/USART2_RX: J7.1, U2.25 (PA3)
/STM32H743VIH6/USART2_TX: J7.2, U2.24 (PA2)
BAT+: J3.1, J6.A4 (VBUS), J6.A9 (VBUS), J6.B4 (VBUS), J6.B9 (VBUS), R28.1, SW2.2 (B)
Boot: R8.1, SW1.2, U2.94 (BOOT0)
GND: C1.1, C2.1, C3.1, C4.1, C5.2, C6.2, C7.2, C8.2, C9.2, C10.2, C11.2, C12.2, C13.2, C14.2, C15.2, C16.2, C19.1, C20.1, C21.2, C22.2, D1.1, D2.1, D8.1 (K), J1.2, J2.2, J3.2, J6.A1 (GND), J6.A12 (GND), J6.B1 (GND), J6.B12 (GND), J6.SH (SHIELD), Q3.2 (E), Q4.2 (S), Q5.2 (E), Q6.2 (S), Q7.2 (E), Q8.2 (S), Q9.2 (E), Q10.2 (S), R8.2, R9.2, R10.1, R11.1, R13.1, R14.1, R25.2, R31.2, R32.2, R33.2, R34.2, U2.10 (VSS), U2.19 (VSSA), U2.26 (VSS), U2.49 (VSS), U2.74 (VSS), U2.99 (VSS), U3.13 (GND), U4.13 (GND), U13.2 (GND), Y1.2
unnamed: C2.2, R1.2, Y2.2
unnamed: C3.2, U2.73 (VCAP)
unnamed: C4.2, U2.48 (VCAP)
unnamed: D1.2, R28.2
unnamed: D2.2, R27.1
unnamed: D3.2 (A), R4.2
unnamed: D3.1 (K), Q4.3 (D)
unnamed: D4.2 (A), R12.2
unnamed: D4.1 (K), Q6.3 (D)
unnamed: D5.2 (A), R19.2
unnamed: D5.1 (K), Q8.3 (D)
unnamed: D6.2 (A), R22.2
unnamed: D6.1 (K), Q10.3 (D)
unnamed: D8.2 (A), R7.2
unnamed: J6.A5 (CC1), R9.1
unnamed: J6.B5 (CC2), R25.1
unnamed: R2.1, Y1.3
unnamed: C1.2, U2.8 (PC14), Y2.1
unnamed: R1.1, U2.9 (PC15)
unnamed: U2.12 (PH0), Y1.1
unnamed: R2.2, U2.13 (PH1)
unnamed: R10.2, U3.3 (AISEN)
unnamed: R13.2, U3.6 (BISEN)
unnamed: C17.2, U3.11 (VCP)
unnamed: C19.2, U3.14 (VINT)
unnamed: R11.2, U4.3 (AISEN)
unnamed: R14.2, U4.6 (BISEN)
unnamed: C18.2, U4.11 (VCP)
unnamed: C20.2, U4.14 (VINT)
PWR: C5.1, J1.5, J2.5, SW2.1 (A), U13.1 (IN)
RxA: Q3.1 (C), R5.2, U2.65 (PC8)
RxB: Q5.1 (C), R6.2, U2.22 (PA0)
RxC: Q9.1 (C), R30.2, U2.59 (PD12)
RxD: Q7.1 (C), R29.2, U2.34 (PB0)
TxA: Q4.1 (G), R31.1, U2.66 (PC9)
TxB: Q6.1 (G), R32.1, U2.23 (PA1)
TxC: Q10.1 (G), R34.1, U2.60 (PD13)
TxD: Q8.1 (G), R33.1, U2.35 (PB1)
USBDM: J6.A7 (D-), J6.B7 (D-), U2.70 (PA11)
USBDP: J6.A6 (D+), J6.B6 (D+), U2.71 (PA12)
nFault: D7.3, U2.16 (PC1)
nFaultx: D7.2, U4.8 (~FAULT)
nFaulty: D7.1, U3.8 (~FAULT)
nSleep: U2.28 (PA4), U3.1 (~SLEEP), U4.1 (~SLEEP)

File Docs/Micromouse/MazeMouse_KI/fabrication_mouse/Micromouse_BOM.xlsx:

Value | Reference | Footprint | JLCPCB Part #
YLED0603R | D8 | LED_SMD:LED_0603_1608Metric | C19171390
USB_C_Receptacle_USB2.0_16P | J6 | -40℃~+85℃ 1 12P 48V 5A Black Female Surface Mount, Right Angle Type-C USB 2.0 S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 | C3020560
AO3400A | Q4 | -55℃~+150℃ 1 N-channel 1.45V 1.4W 30V 48mΩ@2.5V 5.7A 50pF 630pF 75pF 7nC@10V N-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 | C20917
AO3400A | Q6 | -55℃~+150℃ 1 N-channel 1.45V 1.4W 30V 48mΩ@2.5V 5.7A 50pF 630pF 75pF 7nC@10V N-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 | C20917
AO3400A | Q8 | -55℃~+150℃ 1 N-channel 1.45V 1.4W 30V 48mΩ@2.5V 5.7A 50pF 630pF 75pF 7nC@10V N-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 | C20917
AO3400A | Q10 | -55℃~+150℃ 1 N-channel 1.45V 1.4W 30V 48mΩ@2.5V 5.7A 50pF 630pF 75pF 7nC@10V N-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 | C20917
SW_Push | SW1 | - Tactile Switch/Push Button Switch ROHS | C6467298
JS202011CQN | SW2 | Button_Switch_THT:SW_CK_JS202011CQN_DPDT_Straight | C221663
STM32H743VITx | U2 | -40℃~+85℃ 1.71V~3.6V 12bit 16bit 1MB 2MB 32 Bit 480MHz 82 ARM Cortex-M7 Built-i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 | C114409
DRV8833PWP | U3 | -40℃~+85℃ 1.5A 2 2.7V~10.8V 360mΩ Bipolar Driver Yes TSSOP-16-EP Stepper Motor 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 | C50506
DRV8833PWP | U4 | -40℃~+85℃ 1.5A 2 2.7V~10.8V 360mΩ Bipolar Driver Yes TSSOP-16-EP Stepper Motor 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 | C50506
AZ1117CH2-3.3 | U13 | -20℃~+125℃@(Tj) 1 1.2V@(0.8A) 1.35A 15V 3.3V 4mA 70dB@(120Hz) Fixed Over Curren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 | C108492
8MHz Resonator *4MHz* | Y1 | -20℃~+80℃ 39pF 4MHz 60Ω SMD4520-3P Ceramic Resonators ROHS | C91588
32.768 kHz Resonator | Y2 | -40℃~+85℃ 32.768kHz 70kΩ 7pF Crystal Oscillator ±20ppm ±30ppm SMD2012-2P Crysta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 | C5381473
100nF | C7 | PCM_JLCPCB:C_0402 | C1525
100nF | C8 | PCM_JLCPCB:C_0402 | C1525
100nF | C9 | PCM_JLCPCB:C_0402 | C1525
100nF | C10 | PCM_JLCPCB:C_0402 | C1525
100nF | C11 | PCM_JLCPCB:C_0402 | C1525
100nF | C12 | PCM_JLCPCB:C_0402 | C1525
100nF | C13 | PCM_JLCPCB:C_0402 | C1525
100nF | C14 | PCM_JLCPCB:C_0402 | C1525
100nF | C15 | PCM_JLCPCB:C_0402 | C1525
100nF | C16 | PCM_JLCPCB:C_0402 | C1525
10pF | C1 | PCM_JLCPCB:C_0603 | C1634
10pF | C2 | PCM_JLCPCB:C_0603 | C1634
Red | D2 | LED_SMD:LED_0603_1608Metric | C2286
Green | D1 | LED_SMD:LED_0805_2012Metric | C2297
1.8kΩ | R3 | PCM_JLCPCB:R_0603 | C4177
1.8kΩ | R8 | PCM_JLCPCB:R_0603 | C4177
1.8kΩ | R26 | PCM_JLCPCB:R_0603 | C4177
1kΩ | R5 | PCM_JLCPCB:R_0402 | C11702
1kΩ | R6 | PCM_JLCPCB:R_0402 | C11702
1kΩ | R29 | PCM_JLCPCB:R_0402 | C11702
1kΩ | R30 | PCM_JLCPCB:R_0402 | C11702
1kΩ | R31 | PCM_JLCPCB:R_0402 | C11702
1kΩ | R32 | PCM_JLCPCB:R_0402 | C11702
1kΩ | R33 | PCM_JLCPCB:R_0402 | C11702
1kΩ | R34 | PCM_JLCPCB:R_0402 | C11702
2.2uF | C19 | PCM_JLCPCB:C_0402 | C12530
2.2uF | C20 | PCM_JLCPCB:C_0402 | C12530
10nF | C17 | PCM_JLCPCB:C_0402 | C15195
10nF | C18 | PCM_JLCPCB:C_0402 | C15195
10uF | C5 | PCM_JLCPCB:C_0402 | C15525
10uF | C21 | PCM_JLCPCB:C_0402 | C15525
10uF | C22 | PCM_JLCPCB:C_0402 | C15525
0Ω | R10 | PCM_JLCPCB:R_0402 | C17168
0Ω | R11 | PCM_JLCPCB:R_0402 | C17168
0Ω | R13 | PCM_JLCPCB:R_0402 | C17168
0Ω | R14 | PCM_JLCPCB:R_0402 | C17168
100Ω | R1 | PCM_JLCPCB:R_0603 | C22775
100Ω | R2 | PCM_JLCPCB:R_0603 | C22775
240Ω | R7 | PCM_JLCPCB:R_0603 | C23350
240Ω | R27 | PCM_JLCPCB:R_0603 | C23350
240Ω | R28 | PCM_JLCPCB:R_0603 | C23350
2.2uF | C3 | PCM_JLCPCB:C_0603 | C23630
2.2uF | C4 | PCM_JLCPCB:C_0603 | C23630
100Ω | R4 | PCM_JLCPCB:R_0402 | C25076
100Ω | R12 | PCM_JLCPCB:R_0402 | C25076
100Ω | R19 | PCM_JLCPCB:R_0402 | C25076
100Ω | R22 | PCM_JLCPCB:R_0402 | C25076
5.1kΩ | R9 | PCM_JLCPCB:R_0402 | C25905
5.1kΩ | R25 | PCM_JLCPCB:R_0402 | C25905
22uF | C6 | PCM_JLCPCB:C_0603 | C59461
BAT54AW | D7 | PCM_JLCPCB:SOT-323-3_L2.0-W1.3-P1.30-LS2.3-BR | C22466374
